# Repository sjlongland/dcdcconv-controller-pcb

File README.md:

[Find this project on codeberg](https://codeberg.org/sjlongland/dcdcconv-controller-pcb)

As a result of Github's decision to force AI-generated issues with no opt-out,
I am migrating personal projects of mine to Codeberg.  The project at Github
will be archived.

----

# DC-DC Converter Controller

This PCB (using KiCAD 5.0) implements the controller for a DC-DC converter.
It provides differential I²C for connection to a [voltage/current sensor
board](https://codeberg.org/sjlongland/dcdcconv-sensor-pcb) and LVDS outputs for
connection to a [driver
board](https://codeberg.org/sjlongland/dcdcconv-driver-pcb).

The brains of the operation is the Atmel ATTiny861 microcontroller, which
features a high-speed PLL for fast PWM outputs.  The
[firmware](https://codeberg.org/sjlongland/dcdcconv-firmware) polls up to two
sensor boards to make decisions on the PWM duty cycle used to control the
MOSFET driver board.  In theory, the firmware can be expanded to support other
sensor boards and the MOSFET driver board replaced to support other switch
types such as IGBTs for higher power converters.  Use of differential
signalling minimises interference on long cable runs.

The ATTiny861 communicates with a host controller via SPI, allowing it to
communicate with a wide array of host controllers.  This allows for higher-end
host MCUs and application processors that perhaps aren't as good on the PWM
front, to receive notification of when voltage or current levels change
outside given bounds, and thus provide advice on how to adjust the PWM level
to meet requirements.

The host controller can provide the UI functions and higher-level algorithms
such as [MPPT](https://en.wikipedia.org/wiki/Maximum_power_point_tracking)
allowing the ATTiny861 to actually look after the PWM and low-level control.

## Parts list

### To omit:

* U2: Do not fit: for switch controller below only
* C2: Do not fit: localised decoupling for U2.
* J2: Do not fit: GPIO outputs for U2.

### To fit:

* U1: Atmel ATTiny861A-SU
* U3: 74AHC244 tri-state buffer
* U4: NXP PCA9615 Differential I²C controller
* U5: TI SN65LVDS047D 4-channel LVDS driver
* C5: ≥100µF ≥10V 6.3mm SMD electrolytic capacitor (bulk power rail decoupling)
* C1, C3, C4, C6: 100nF ≥10V 0805 ceramic capacitor (localised power rail
  decoupling)
* (**FIT ONE ONLY**) C7, C8, C9, C10: ~100pF ≥20V ceramic capacitor 0805 (0V
  AC de-coupling to chassis.  Choose the one that best suits your mounting
  requirements.)
* R1, R2: 2k2 ohm resistors, 0805 size (I²C pull-ups)
* R3, R4, R5, R6, R7: (approx) 10k ohm resistors, 0805 size (GPIO pull-ups)
* R8, R10: (**NOT CONFIRMED**) 2k2 ohm resistors, 0805 size (differential I²C
  pull-ups)
* R12, R15: (**NOT CONFIRMED**) 2k2 ohm resistors, 0805 size (differential I²C
  pull-downs)
* R9, R11, R12, R14: Spaces for additional pull-up/down resistors on
  differential I²C.  Do not fit unless found to be required.
* R16, R17: (**NOT CONFIRMED**) 100 ohm 0805 (differential I²C termination)
* R22, R26, R30, R34, R24, R28, R32, R36: Spaces for pull-up resistors on
  LVDS.  Do not fit unless found to be required.
* R23, R27, R31, R35, R25, R29, R33, R37: Spaces for pull-down resistors on
  LVDS.  Do not fit unless found to be required.
* R18, R19, R20, R21: Spaces for termination resistors on LVDS.  Do not fit
  unless found to be required.
* J1: 2×7 right-angle 2.54mm header connector (host SPI interface)
* J3, J4: 6-pin 2.54mm "KK" connector (Differential I²C to sensor boards,
  two provided for wiring convenience wired in parallel, use both or
  either.)
* J5: 6-pin 2.54mm "KK" connector (LVDS PWM outputs for buck converter
  MOSFETs)
* J6: 6-pin 2.54mm "KK" connector (LVDS PWM outputs for boost converter
  MOSFETs)

# Switch controller

The board also supports an alternate MCU, the Atmel ATTiny24A, which can be
used in place of the ATTiny861 for simple switch control.  In this
configuration, the LVDS output is dispensed with in favour of a pair of
low-speed GPIOs (one PWMable) which can drive a small signal transistor for
MOSFET control or directly drive solid-state relays.

This latter design is intended for applications such as
[VSRs](https://en.wikipedia.org/wiki/Voltage-sensitive_relay) and power
distribution control using an interface compatible with the full controller.
The controller still supports talking to multiple sensor boards for power
measurement.

## Parts list

### To omit:
* C1, C4, C6: Do not fit: localised decoupling for U1, U3, U5.
* U1, U3, U5: Do not fit: for PWM DC-DC controller above.
* R22, R26, R30, R34, R24, R28, R32, R36, R23, R27, R31, R35, R25, R29, R33,
  R37, R18, R19, R20, R21: Do not fit: pull resistors for LVDS (not used)
* J5, J6: Do not fit: LVDS outputs for PWM controller

### To fit:
* U2: Atmel ATTiny24A-SSU
* U4: NXP PCA9615 Differential I²C controller
* C5: ≥100µF ≥10V 6.3mm SMD electrolytic capacitor (bulk power rail decoupling)
* C2, C3: 100nF ≥10V 0805 ceramic capacitor (localised power rail
  decoupling)
* (**FIT ONE ONLY**) C7, C8, C9, C10: ~100pF ≥20V ceramic capacitor 0805 (0V
  AC de-coupling to chassis.  Choose the one that best suits your mounting
  requirements.)
* R1, R2: 2k2 ohm resistors, 0805 size (I²C pull-ups)
* R3, R4, R5, R6, R7: (approx) 10k ohm resistors, 0805 size (GPIO pull-ups)
* R8, R10: (**NOT CONFIRMED**) 2k2 ohm resistors, 0805 size (differential I²C
  pull-ups)
* R12, R15: (**NOT CONFIRMED**) 2k2 ohm resistors, 0805 size (differential I²C
  pull-downs)
* R9, R11, R12, R14: Spaces for additional pull-up/down resistors on
  differential I²C.  Do not fit unless found to be required.
* R16, R17: (**NOT CONFIRMED**) 100 ohm 0805 (differential I²C termination)
* J1: 2×7 right-angle 2.54mm header connector (host SPI interface)
* J2: 4-pin 2.54mm "KK" connector (GPIO outputs for MOSFET/SSR switch control)
* J3, J4: 6-pin 2.54mm "KK" connector (Differential I²C to sensor boards,
  two provided for wiring convenience wired in parallel, use both or
  either.)

# Host interface

The host interface is via the 14-pin connector at the bottom of the board.
This connector features the following signals:

* Even pins: 0V reference voltage
* Pin 1: 5V power rail
* Pin 3: SPI interface `MOSI` data input
* Pin 5: SPI interface `MISO` data output
* Pin 7: SPI interface `SCK` serial clock
* Pin 9: SPI interface `nCS` Chip select
* Pin 11: SPI interface `nINT` Host interrupt
* Pin 13: `nRESET` Device reset and AVR ICSP.
* Pin 15: `GPIO1` Arbitrary GPIO for application use
* Pin 17: `GPIO0` Arbitrary GPIO for application use

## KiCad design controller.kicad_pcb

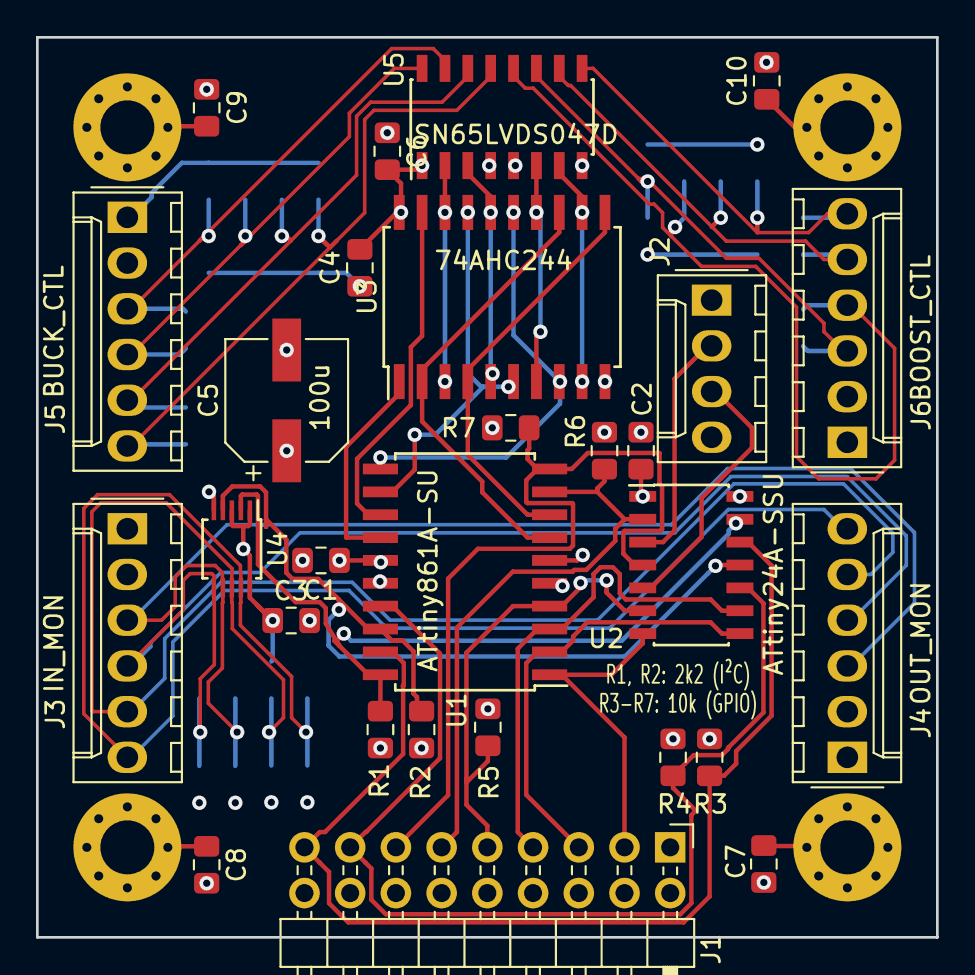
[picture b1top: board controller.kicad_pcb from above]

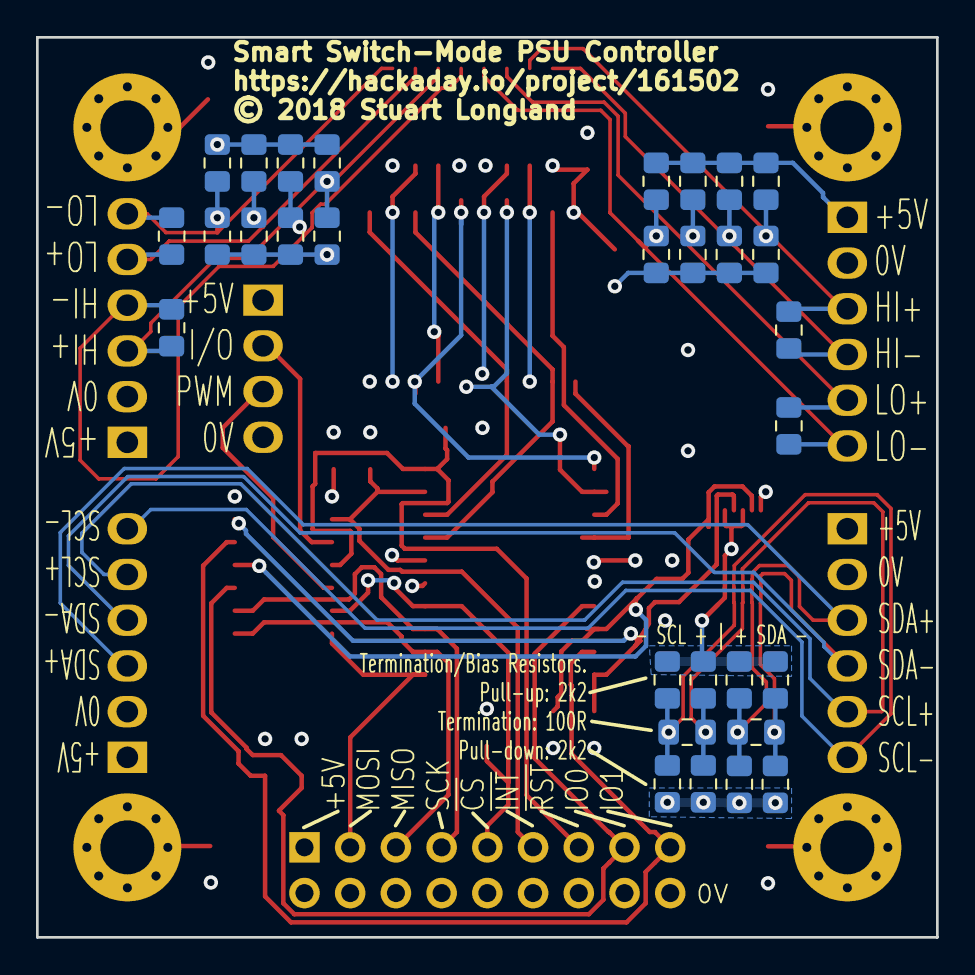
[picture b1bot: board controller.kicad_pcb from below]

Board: 4 copper layers, 50.0 x 50.0 mm, 62 parts (30 on the bottom side), 40 nets.

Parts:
C1, C2, C3, C4, C6: 100n; C_0805_2012Metric_Pad1.15x1.40mm_HandSolder
C5: 100u; CP_Elec_6.3x9.9
C7, C8, C9, C10: 10p; C_0805_2012Metric_Pad1.15x1.40mm_HandSolder
J1: Conn_02x07_Odd_Even; PinHeader_2x09_P2.54mm_Horizontal
J2: Conn_01x04; Molex_KK-254_AE-6410-04A_1x04_P2.54mm_Vertical
J3: IN_MON; Molex_KK-254_AE-6410-06A_1x06_P2.54mm_Vertical
J4: OUT_MON; Molex_KK-254_AE-6410-06A_1x06_P2.54mm_Vertical
J5: BUCK_CTL; Molex_KK-254_AE-6410-06A_1x06_P2.54mm_Vertical
J6: BOOST_CTL; Molex_KK-254_AE-6410-06A_1x06_P2.54mm_Vertical
MH1, MH2, MH3, MH4: MountingHole_Pad; MountingHole_3mm_Pad_Via
R1, R2, R8, R9, R10, R11, R12, R13, R14, R15, R22, R23, R24, R25, R26, R27, R28, R29, R30, R31, R32, R33, R34, R35, R36, R37: 2k2; R_0805_2012Metric_Pad1.15x1.40mm_HandSolder
R3, R4, R5, R6, R7: 10k; R_0805_2012Metric_Pad1.15x1.40mm_HandSolder
R16, R17, R18, R19, R20, R21: 100R; R_0805_2012Metric_Pad1.15x1.40mm_HandSolder
U1: ATtiny861A-SU; SOIC-20W_7.5x12.8mm_P1.27mm
U2: ATtiny24A-SSU; SOIC-14_3.9x8.7mm_P1.27mm
U3: 74AHC244; SOIC-20W_7.5x12.8mm_P1.27mm
U4: PCA9615; TSSOP-10_3x3mm_P0.5mm
U5: SN65LVDS047D; SOIC-16_3.9x9.9mm_P1.27mm

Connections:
/BOOST_HI: U3.7, U3.14, U5.6
/BOOST_HI+: J6.3, R20.2, R24.2, R25.1, U5.11
/BOOST_HI-: J6.4, R20.1, R28.2, R29.1, U5.12
/BOOST_LO: U3.9, U3.12, U5.7
/BOOST_LO+: J6.5, R21.2, R32.2, R33.1, U5.10
/BOOST_LO-: J6.6, R21.1, R36.2, R37.1, U5.9
/BUCK_HI: U3.3, U3.18, U5.2
/BUCK_HI+: J5.3, R18.2, R22.2, R23.1, U5.15
/BUCK_HI-: J5.4, R18.1, R26.2, R27.1, U5.16
/BUCK_LO: U3.5, U3.16, U5.3
/BUCK_LO+: J5.5, R19.1, R30.2, R31.1, U5.14
/BUCK_LO-: J5.6, R19.2, R34.2, R35.1, U5.13
/GPIO0: J1.17, R3.2, U1.19, U2.12
/GPIO1: J1.15, R4.2, U1.17, U2.10
/HI_DRV: U1.12, U3.6, U3.17
/LO_DRV: U1.11, U3.8, U3.15
/MISO: J1.5, U1.2, U2.8
/MOSI: J1.3, U1.1, U2.7
/PWM: U1.8, U3.4, U3.11
/SCK: J1.7, U1.3, U2.9
/SCL: R2.2, U1.18, U2.11, U4.4
/SCL+: J3.5, J4.5, R10.2, R14.1, R17.2, U4.8
/SCL-: J3.6, J4.6, R11.2, R15.1, R17.1, U4.9
/SDA: R1.2, U1.20, U2.13, U4.2
/SDA+: J3.3, J4.3, R8.2, R12.1, R16.1, U4.7
/SDA-: J3.4, J4.4, R9.2, R13.1, R16.2, U4.6
/T24_IO: J2.2, U2.3
/T24_PWM: J2.3, U2.5
/~BOOST_PWM_EN~: U1.13, U3.19
/~BUCK_PWM_EN~: U1.14, U3.1
/~CS~: J1.9, R5.2, U1.4, U2.6
/~INT~: J1.11, R6.2, U1.9, U2.2
/~PWM~: U1.7, U3.2, U3.13
/~RESET~: J1.13, R7.2, U1.10, U2.4
GND: C1.2, C2.2, C3.2, C4.1, C5.2, C6.1, C7.2, C8.2, C9.2, C10.2, J1.2, J1.4, J1.6, J1.8, J1.10, J1.12, J1.14, J1.16, J1.18, J2.4, J3.2, J4.2, J5.2, J6.2, R12.2, R13.2, R14.2, R15.2, R23.2, R25.2, R27.2, R29.2, R31.2, R33.2, R35.2, R37.2, U1.6, U1.16, U2.14, U3.10, U4.5, U5.5, U5.8
unnamed: C7.1, MH1.1
unnamed: C8.1, MH2.1
unnamed: C9.1, MH3.1
unnamed: C10.1, MH4.1
VCC: C1.1, C2.1, C3.1, C4.2, C5.1, C6.2, J1.1, J2.1, J3.1, J4.1, J5.1, J6.1, R1.1, R2.1, R3.1, R4.1, R5.1, R6.1, R7.1, R8.1, R9.1, R10.1, R11.1, R22.1, R24.1, R26.1, R28.1, R30.1, R32.1, R34.1, R36.1, U1.5, U1.15, U2.1, U3.20, U4.1, U4.3, U4.10, U5.1, U5.4

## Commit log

2018-10-07 Initial check-in
2018-10-07 VCC plane: Move in by 1mm.
    This should reduce any possibility of EMI "leaking" from the VCC plane.
2018-10-22 PCB: Finalise layout
2018-10-22 gerber: Add CAM files for production.
2025-05-30 README.md: update regarding move of project

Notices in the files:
controller.kicad_pcb:
© 2018 Stuart Longland
